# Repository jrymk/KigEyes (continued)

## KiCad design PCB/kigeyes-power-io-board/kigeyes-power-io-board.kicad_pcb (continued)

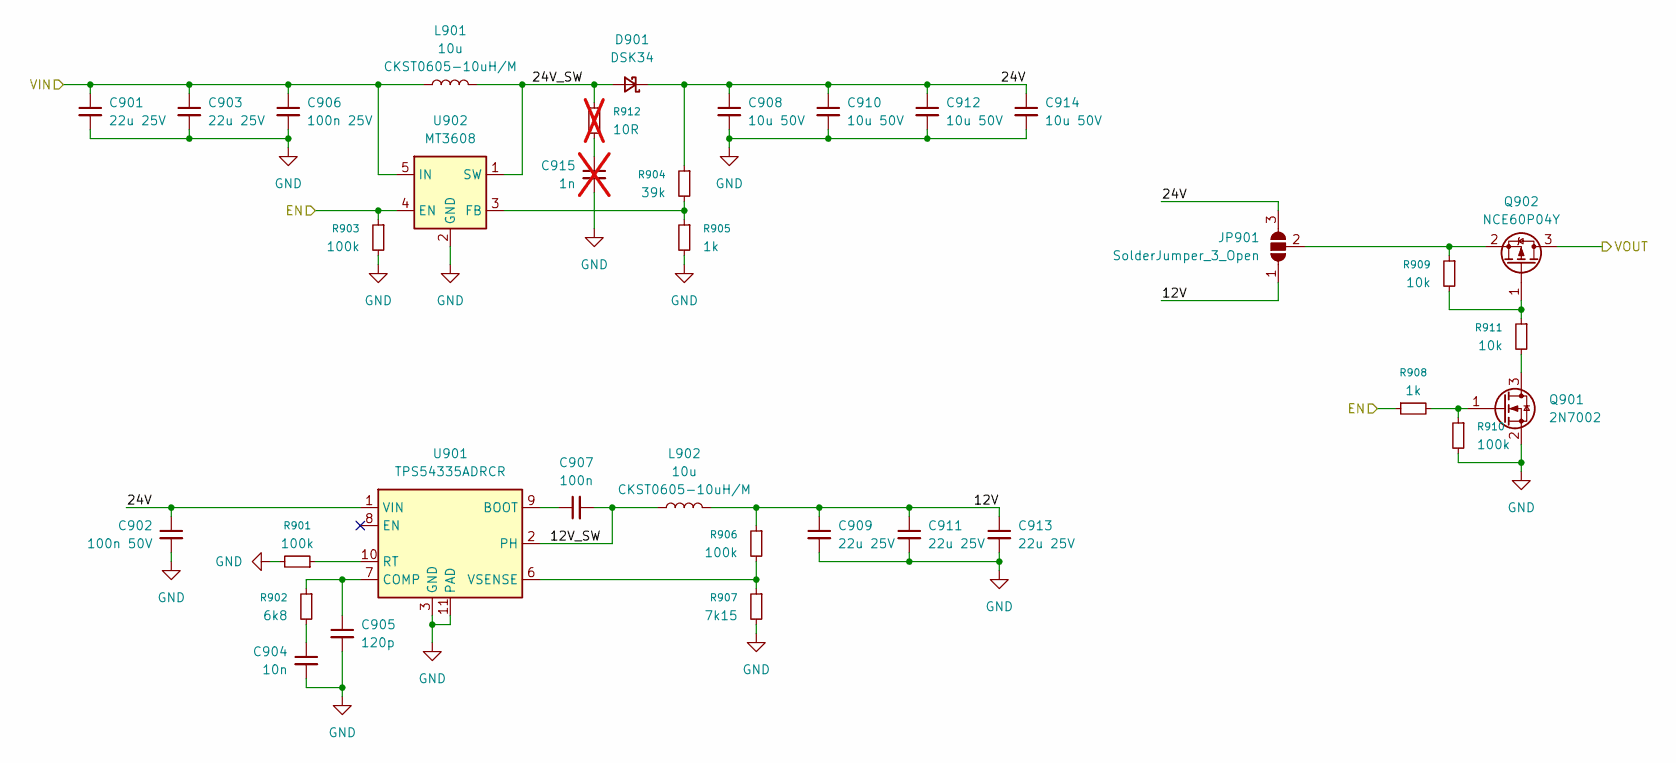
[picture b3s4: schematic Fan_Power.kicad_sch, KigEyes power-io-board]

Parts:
C901, C903, C909, C911, C913: 22u 25V; C_0805_2012Metric
C902: 100n 50V; C_0603_1608Metric
C904: 10n; C_0402_1005Metric
C905: 120p; C_0402_1005Metric
C906: 100n 25V; C_0603_1608Metric
C907: 100n; C_0402_1005Metric
C908, C910, C912, C914: 10u 50V; C_0805_2012Metric
C915: 1n; C_0402_1005Metric; not fitted
D901: DSK34; D_SOD-123FL
JP901: SolderJumper_3_Open; SolderJumper-3_P1.3mm_Open_RoundedPad1.0x1.5mm
L901, L902: 10u; L_CKST0605; Part No. CKST0605-10uH/M
Q901: 2N7002; SOT-23
Q902: NCE60P04Y; SOT-23
R901, R903, R906, R910: 100k; R_0402_1005Metric
R902: 6k8; R_0402_1005Metric
R904: 39k; R_0402_1005Metric
R905, R908: 1k; R_0402_1005Metric
R907: 7k15; R_0402_1005Metric
R909, R911: 10k; R_0402_1005Metric
R912: 10R; R_0402_1005Metric; not fitted
U901: TPS54335ADRCR; Texas_DRC0010J
U902: MT3608; SOT-23-6

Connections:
/AON_5V_OR_HV: C901.1, C903.1, C906.1, L901.1, U902.5 (IN); also elsewhere on the board
/FAN_EN: R903.1, R908.1, U902.4 (EN); also elsewhere on the board
/Fan Power/12V: C909.1, C911.1, C913.1, JP901.1 (A), L902.2, R906.1
/Fan Power/12V_SW: C907.2, L902.1, U901.2 (PH)
/Fan Power/24V: C902.1, C908.1, C910.1, C912.1, C914.1, D901.1 (K), JP901.3 (B), R904.1, U901.1 (VIN)
/Fan Power/24V_SW: D901.2 (A), L901.2, R912.1, U902.1 (SW)
/Fan Power/VOUT: Q902.3 (D); also elsewhere on the board
GND: C901.2, C902.2, C903.2, C904.2, C905.2, C906.2, C908.2, C909.2, C910.2, C911.2, C912.2, C913.2, C914.2, C915.2, Q901.2 (S), R901.2, R903.2, R905.2, R907.2, R910.2, U901.3 (GND), U901.4 (GND), U901.5 (GND), U901.11 (PAD), U902.2 (GND); also elsewhere on the board
unnamed: C904.1, R902.2
unnamed: C915.1, R912.2
unnamed: JP901.2 (C), Q902.2 (S), R909.1
unnamed: Q901.3 (D), R911.2
unnamed: Q901.1 (G), R908.2, R910.1
unnamed: Q902.1 (G), R909.2, R911.1
unnamed: C907.1, U901.9 (BOOT)
unnamed: C905.1, R902.1, U901.7 (COMP)
unnamed: R901.1, U901.10 (RT)
unnamed: R906.2, R907.1, U901.6 (VSENSE)
unnamed: R904.2, R905.1, U902.3 (FB)

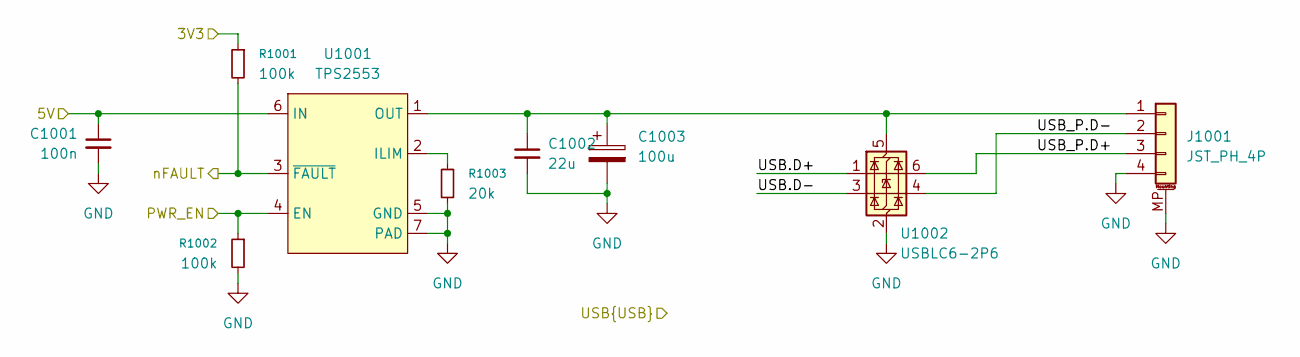
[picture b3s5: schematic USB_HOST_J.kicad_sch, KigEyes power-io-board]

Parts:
C1001: 100n; C_0402_1005Metric
C1002: 22u; C_0603_1608Metric
C1003: 100u; CP_Elec_6.3x5.8
J1001: JST_PH_4P; JST_PH_S4B-PH-SM4-TB_1x04-1MP_P2.00mm_Horizontal
R1001, R1002: 100k; R_0402_1005Metric
R1003: 20k; R_0402_1005Metric
U1001: TPS2553; WSON-6-1EP_2x2mm_P0.65mm_EP1x1.6mm
U1002: USBLC6-2P6; SOT-666

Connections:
+3V3: R1001.1; also elsewhere on the board
+5V: C1001.1, U1001.6 (IN); also elsewhere on the board
/PORT3_OCS: R1001.2, U1001.3 (~FAULT); also elsewhere on the board
/PORT3_PWR: R1002.1, U1001.4 (EN); also elsewhere on the board
/USB_HOST_J.D+: U1002.1 (I/O1); also elsewhere on the board
/USB_HOST_J.D-: U1002.3 (I/O2); also elsewhere on the board
/USB_HOST_J/USB_P.D+: J1001.3, U1002.6 (I/O1)
/USB_HOST_J/USB_P.D-: J1001.2, U1002.4 (I/O2)
GND: C1001.2, C1002.2, C1003.2, J1001.4, J1001.MP (MountPin), R1002.2, R1003.2, U1001.5 (GND), U1001.7 (PAD), U1002.2 (GND); also elsewhere on the board
unnamed: C1002.1, C1003.1, J1001.1, U1001.1 (OUT), U1002.5 (VBUS)
unnamed: R1003.1, U1001.2 (ILIM)

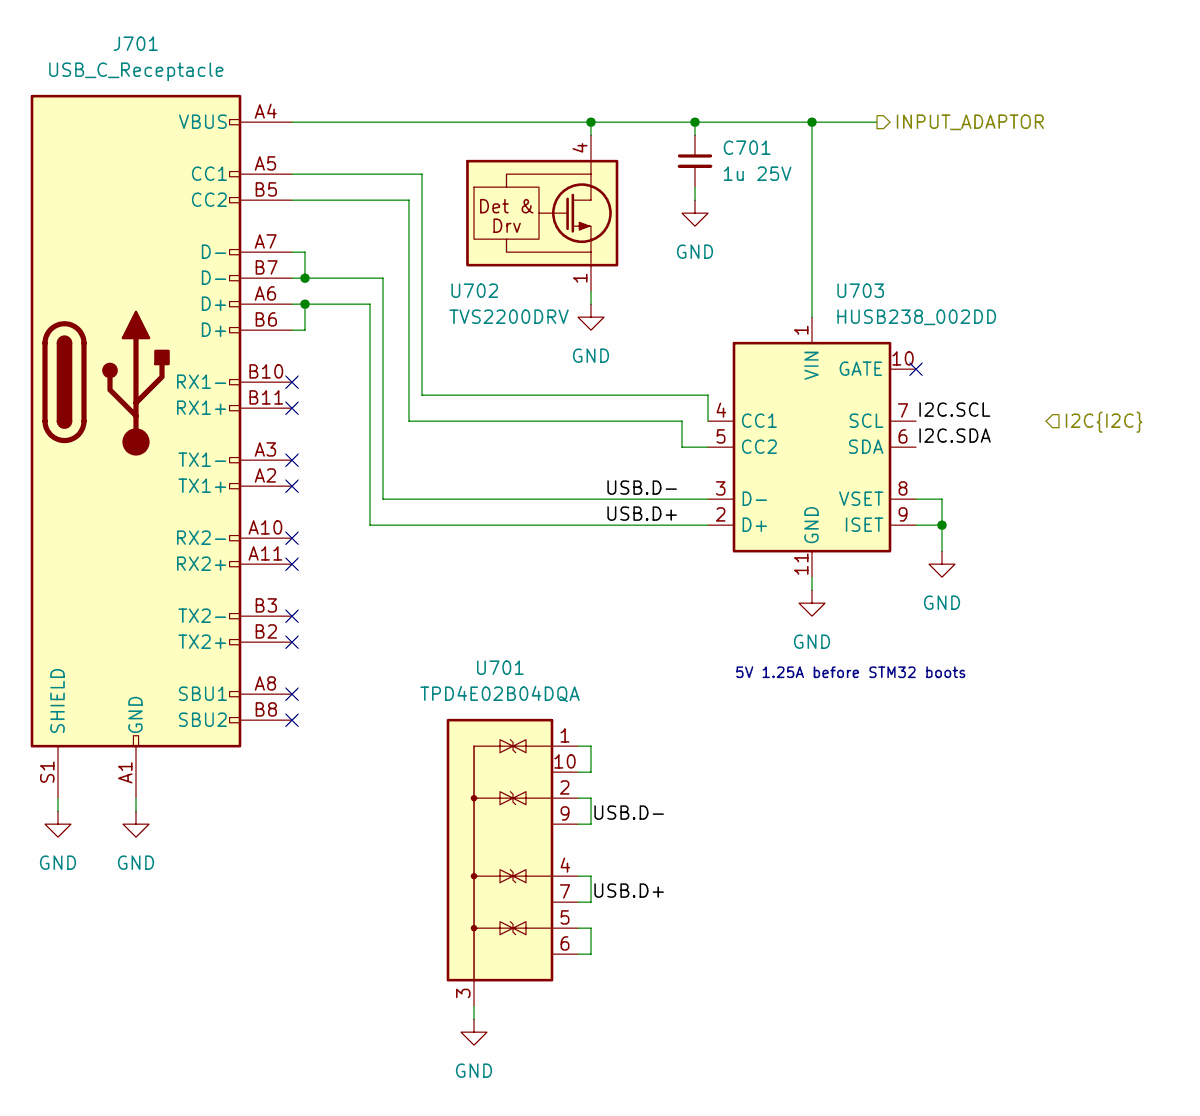
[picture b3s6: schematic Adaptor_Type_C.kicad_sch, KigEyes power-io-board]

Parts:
C701: 1u 25V; C_0603_1608Metric
J701: USB_C_Receptacle; USB_C_Receptacle_GCT_USB4080
U701: TPD4E02B04DQA; Texas USON-10_2.5x1.0mm_P0.5mm DQA0010A
U702: TVS2200DRV; WSON-6-1EP_2x2mm_P0.65mm_EP1x1.6mm
U703: HUSB238_002DD; WDFN-10-1EP_3x3mm_P0.5mm_EP1.8x2.5mm

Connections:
/Adaptor Type C/USB.D+: J701.A6 (D+), J701.B6 (D+), U701.4 (IO3), U701.7 (NC), U703.2 (D+)
/Adaptor Type C/USB.D-: J701.A7 (D-), J701.B7 (D-), U701.2 (IO2), U701.9 (NC), U703.3 (D-)
/I2C.SCL: U703.7 (SCL); also elsewhere on the board
/I2C.SDA: U703.6 (SDA); also elsewhere on the board
/INPUT_ADAPTOR: C701.1, J701.A4 (VBUS), J701.A9 (VBUS), J701.B4 (VBUS), J701.B9 (VBUS), U702.4 (IN), U702.5 (IN), U702.6 (IN), U703.1 (VIN); also elsewhere on the board
GND: C701.2, J701.A1 (GND), J701.A12 (GND), J701.B1 (GND), J701.B12 (GND), J701.S1 (SHIELD), U701.3 (G), U701.8 (G), U702.1 (GND), U702.2 (GND), U702.3 (GND), U702.7 (GND), U703.8 (VSET), U703.9 (ISET), U703.11 (GND); also elsewhere on the board
unnamed: J701.A5 (CC1), U703.4 (CC1)
unnamed: J701.B5 (CC2), U703.5 (CC2)
unnamed: U701.1 (IO1), U701.10 (NC)
unnamed: U701.5 (IO4), U701.6 (NC)

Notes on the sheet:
5V 1.25A before STM32 boots

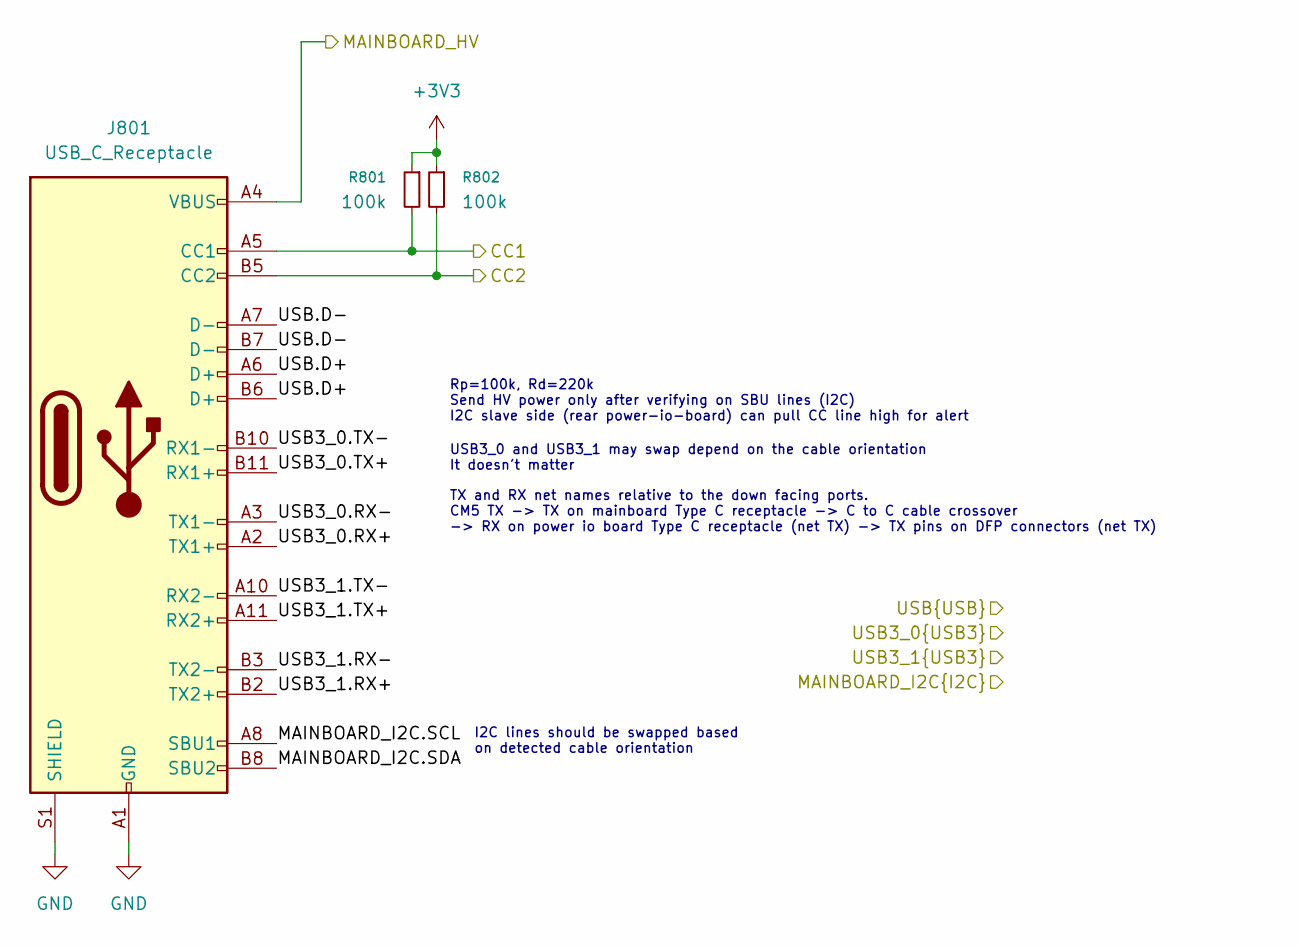
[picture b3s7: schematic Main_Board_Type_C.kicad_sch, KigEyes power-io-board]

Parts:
J801: USB_C_Receptacle; USB_C_Receptacle_GCT_USB4080
R801, R802: 100k; R_0402_1005Metric

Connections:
+3V3: R801.1, R802.1; also elsewhere on the board
/CC1: J801.A5 (CC1), R801.2; also elsewhere on the board
/CC2: J801.B5 (CC2), R802.2; also elsewhere on the board
/MAINBOARD_HV: J801.A4 (VBUS), J801.A9 (VBUS), J801.B4 (VBUS), J801.B9 (VBUS); also elsewhere on the board
/MAINBOARD_I2C.SCL: J801.A8 (SBU1); also elsewhere on the board
/MAINBOARD_I2C.SDA: J801.B8 (SBU2); also elsewhere on the board
/USB3_0.RX+: J801.A2 (TX1+); also elsewhere on the board
/USB3_0.RX-: J801.A3 (TX1-); also elsewhere on the board
/USB3_0.TX+: J801.B11 (RX1+); also elsewhere on the board
/USB3_0.TX-: J801.B10 (RX1-); also elsewhere on the board
/USB3_1.RX+: J801.B2 (TX2+); also elsewhere on the board
/USB3_1.RX-: J801.B3 (TX2-); also elsewhere on the board
/USB3_1.TX+: J801.A11 (RX2+); also elsewhere on the board
/USB3_1.TX-: J801.A10 (RX2-); also elsewhere on the board
/USB.D+: J801.A6 (D+), J801.B6 (D+); also elsewhere on the board
/USB.D-: J801.A7 (D-), J801.B7 (D-); also elsewhere on the board
GND: J801.A1 (GND), J801.A12 (GND), J801.B1 (GND), J801.B12 (GND), J801.S1 (SHIELD); also elsewhere on the board

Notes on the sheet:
TX and RX net names relative to the down facing ports. CM5 TX -> TX on mainboard Type C receptacle -> C to C cable crossover -> RX on power io board Type C receptacle (net TX) -> TX pins on DFP connectors (net TX)
I2C lines should be swapped based on detected cable orientation
Rp=100k, Rd=220k Send HV power only after verifying on SBU lines (I2C) I2C slave side (rear power-io-board) can pull CC line high for alert
USB3_0 and USB3_1 may swap depend on the cable orientation It doesn't matter

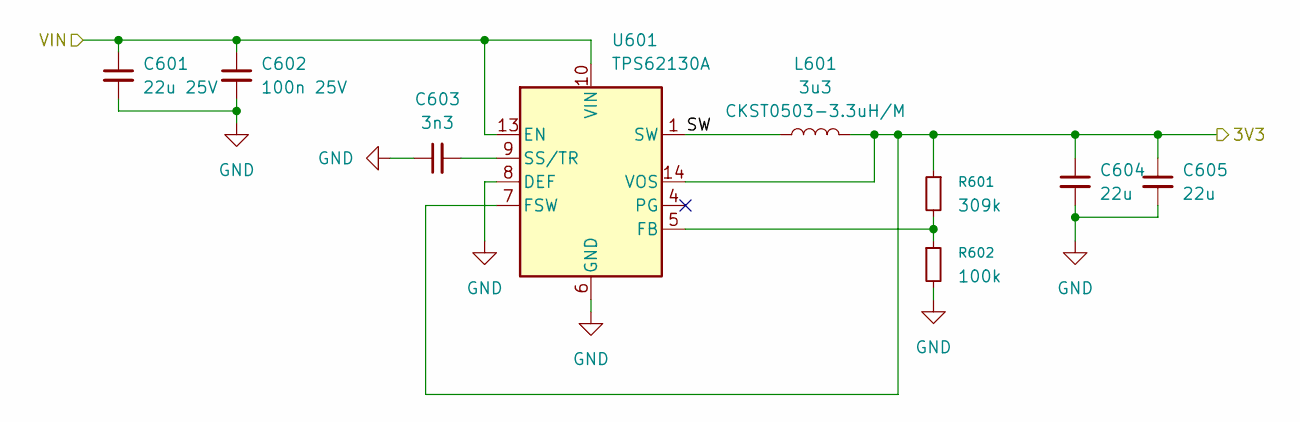
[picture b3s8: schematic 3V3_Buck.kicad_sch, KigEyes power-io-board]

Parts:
C601: 22u 25V; C_0805_2012Metric
C602: 100n 25V; C_0603_1608Metric
C603: 3n3; C_0402_1005Metric
C604, C605: 22u; C_0603_1608Metric
L601: 3u3; L_CKST0503; Part No. CKST0503-3.3uH/M
R601: 309k; R_0402_1005Metric
R602: 100k; R_0402_1005Metric
U601: TPS62130A; VQFN-16-1EP_3x3mm_P0.5mm_EP1.68x1.68mm

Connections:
+3V3: C604.1, C605.1, L601.2, R601.1, U601.7 (FSW), U601.14 (VOS); also elsewhere on the board
/3V3 Buck/SW: L601.1, U601.1 (SW), U601.2 (SW), U601.3 (SW)
/AON_5V_OR_HV: C601.1, C602.1, U601.10 (VIN), U601.11 (VIN), U601.12 (VIN), U601.13 (EN); also elsewhere on the board
GND: C601.2, C602.2, C603.1, C604.2, C605.2, R602.2, U601.6 (GND), U601.8 (DEF), U601.15 (GND), U601.16 (GND), U601.17 (GND); also elsewhere on the board
unnamed: R601.2, R602.1, U601.5 (FB)
unnamed: C603.2, U601.9 (SS/TR)

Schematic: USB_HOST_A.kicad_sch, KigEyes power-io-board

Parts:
C301: 100n; C_0402_1005Metric
C302: 22u; C_0603_1608Metric
C303: 100u; CP_Elec_6.3x5.8
J301: USB3_A; USB3_A_GCT-USB1135
R301, R302: 100k; R_0402_1005Metric
R303: 20k; R_0402_1005Metric
U301: TPS2553; WSON-6-1EP_2x2mm_P0.65mm_EP1x1.6mm
U302: USBLC6-2P6; SOT-666
U303: TPD4E02B04DQA; Texas USON-10_2.5x1.0mm_P0.5mm DQA0010A

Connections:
+3V3: R301.1; also elsewhere on the board
+5V: C301.1, U301.6 (IN); also elsewhere on the board
/PORT2_OCS: R301.2, U301.3 (~FAULT); also elsewhere on the board
/PORT2_PWR: R302.1, U301.4 (EN); also elsewhere on the board
/USB3_1.RX+: J301.6 (SSRX+), U303.2 (IO2), U303.9 (NC); also elsewhere on the board
/USB3_1.RX-: J301.5 (SSRX-), U303.1 (IO1), U303.10 (NC); also elsewhere on the board
/USB3_1.TX+: J301.9 (SSTX+), U303.5 (IO4), U303.6 (NC); also elsewhere on the board
/USB3_1.TX-: J301.8 (SSTX-), U303.4 (IO3), U303.7 (NC); also elsewhere on the board
/USB_HOST_A.D+: U302.6 (I/O1); also elsewhere on the board
/USB_HOST_A.D-: U302.4 (I/O2); also elsewhere on the board
/USB_HOST_A/USB_P.D+: J301.3 (D+), U302.1 (I/O1)
/USB_HOST_A/USB_P.D-: J301.2 (D-), U302.3 (I/O2)
GND: C301.2, C302.2, C303.2, J301.4 (GND), J301.7 (DRAIN), J301.SH (SHIELD), R302.2, R303.2, U301.5 (GND), U301.7 (PAD), U302.2 (GND), U303.3 (G), U303.8 (G); also elsewhere on the board
unnamed: C302.1, C303.1, J301.1 (VBUS), U301.1 (OUT), U302.5 (VBUS)
unnamed: R303.1, U301.2 (ILIM)

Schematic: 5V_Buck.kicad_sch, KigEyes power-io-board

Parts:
C501, C502, C503: 22u 25V; C_0805_2012Metric
C504: 100n 25V; C_0603_1608Metric
C505: 47n; C_0402_1005Metric
C506: 1u; C_0402_1005Metric
C507: 100n; C_0402_1005Metric
C508: 47p; C_0402_1005Metric
C509, C510: 100u; C_1210_3225Metric
L501: 2u2; L_CKST1004; Part No. CKST1004-2.2uH/M
R501: 330k; R_0402_1005Metric
R502, R505: 15k; R_0402_1005Metric
R503: 100k; R_0402_1005Metric
R504: 110k; R_0402_1005Metric
U501: TPS56C230; VQFN-20_EP_3x3_Pitch0.45mm_RJE0020B

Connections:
+5V: C508.1, C509.1, C510.1, L501.2, R504.1; also elsewhere on the board
/5V Buck/PGOOD: U501.9 (PGOOD)
/5V Buck/SW: C507.2, L501.1, U501.6 (SW), U501.19 (SW), U501.20 (SW)
/5V Buck/VCC: C506.2, R501.1, U501.17 (VCC)
/5V_EN: R503.1, U501.12 (EN); also elsewhere on the board
/AON_5V_OR_HV: C501.1, C502.1, C503.1, C504.1, U501.2 (VIN), U501.3 (VIN), U501.4 (VIN), U501.5 (VIN); also elsewhere on the board
GND: C501.2, C502.2, C503.2, C504.2, C505.2, C506.1, C509.2, C510.2, R502.2, R503.2, R505.2, U501.7 (PGND), U501.8 (PGND), U501.10 (NC), U501.13 (AGND), U501.16 (NC), U501.18 (PGND), U501.21 (PGND); also elsewhere on the board
unnamed: C507.1, U501.1 (BST)
unnamed: C508.2, R504.2, R505.1, U501.14 (FB)
unnamed: R501.2, R502.1, U501.15 (MODE)
unnamed: C505.1, U501.11 (SS)

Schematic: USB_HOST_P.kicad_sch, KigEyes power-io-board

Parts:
C1102: 22u; C_0603_1608Metric
J1101: Conn_01x04_MountingPin; JST_PH_B4B-PH-K_1x04_P2.00mm_Vertical
U1102: USBLC6-2P6; SOT-666

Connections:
+5V: C1102.1, J1101.1, U1102.5 (VBUS); also elsewhere on the board
/USB_HOST_P.D+: U1102.1 (I/O1); also elsewhere on the board
/USB_HOST_P.D-: U1102.3 (I/O2); also elsewhere on the board
/USB_HOST_P/USB_P.D+: J1101.3, U1102.6 (I/O1)
/USB_HOST_P/USB_P.D-: J1101.2, U1102.4 (I/O2)
GND: C1102.2, J1101.4, U1102.2 (GND); also elsewhere on the board

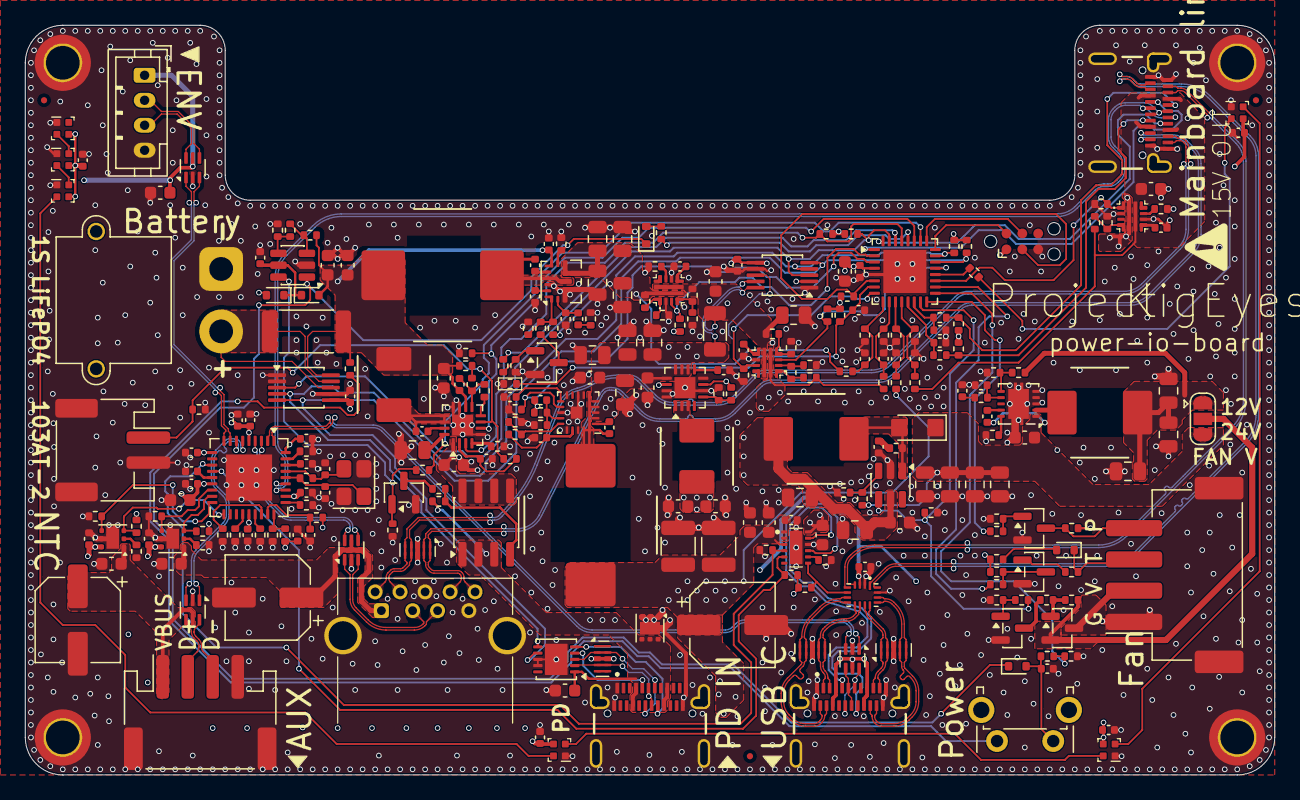
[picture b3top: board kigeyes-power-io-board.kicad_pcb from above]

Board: 4 copper layers, 100.0 x 60.0 mm, 280 parts (0 on the bottom side), 184 nets.

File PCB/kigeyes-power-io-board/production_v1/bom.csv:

Designator,Footprint,Quantity,Value,LCSC Part #
"C1001, C103, C105, C122, C128, C129, C132, C204, C205, C301, C403, C404, C408, C409, C410, C411, C412, C413, C507, C907",0402,20,100n,
"C1002, C101, C102, C1102, C202, C203, C302, C604, C605",0603,9,22u,
"C1003, C201, C303",CP_Elec_6.3x5.8,3,100u,
"C104, C107",0402,2,2u2,
"C106, C126, C133",0603,3,2u2 25V,
C108,0402,1,1n,
"C109, C110, C114, C120, C123, C131, C139",0402,7,10n,
C111,0805,1,10u 25V,
C112,0402,1,30p,
"C113, C116, C119, C121, C501, C502, C503, C601, C901, C903, C909, C911, C913",0805,13,22u 25V,
"C115, C505",0402,2,47n,
C117,0402,1,470p,
C118,0603,1,10u,
"C124, C125, C130, C603",0402,4,3n3,
"C127, C206, C414",0603,3,4u7,
"C134, C135, C136, C137, C138, C406, C407, C506",0402,8,1u,
"C401, C402",0402,2,15p,
C405,0402,1,220n,
"C504, C602, C906",0603,3,100n 25V,
C508,0402,1,47p,
"C509, C510",1210,2,100u,
C701,0603,1,1u 25V,
C902,0603,1,100n 50V,
C904,0402,1,12n,
C905,0402,1,120p,
"C908, C910, C912, C914",0805,4,10u 50V,
"D101, D102, D103, D104, D105",D_SOD-523,5,SD103AWT,
"D106, D107, D108, D109, D110, D111",WS2812B-1515,6,WS2812B,
D901,D_SOD-123FL,1,DSK34,
J1001,JST_PH_S4B-PH-SM4-TB_1x04-1MP_P2.00mm_Horizontal,1,Conn_01x04_MountingPin,
J101,JST_PH_S2B-PH-SM4-TB_1x02-1MP_P2.00mm_Horizontal,1,Conn_01x02_MountingPin,
J102,AMASS_XT30PW-M_1x02_P2.50mm_Horizontal,1,XT30,
J104,JST_XH_S4B-XH-SM4-TB_1x04-1MP_P2.50mm_Horizontal,1,JST_PH_4P,
J1101,JST_PH_B4B-PH-K_1x04_P2.00mm_Vertical,1,Conn_01x04_MountingPin,
"J201, J701, J801",USB_C_Receptacle_GCT_USB4080,3,USB_C_Receptacle,
J301,USB3_A_GCT-USB1135,1,USB3_A,
"L101, L501",L_CKST1004,2,2u2,
L102,L_CKST0503,1,2u2,
L601,L_CKST0503,1,3u3,
"L901, L902",L_CKST0605,2,10u,
"Q101, Q104, Q901",SOT-23,3,2N7002,
Q102,SOP-8_3.76x4.96mm_P1.27mm_NCE40P13S,1,NCE40P13S,
Q103,SOT-23,1,AO3400A,
Q105,SOT-23,1,MMBT3904,
Q902,SOT-23,1,NCE60P04Y,
"R1001, R1002, R104, R106, R113, R118, R131, R135, R140, R150, R161, R162, R163, R165, R168, R169, R201, R202, R203, R204, R301, R302, R402, R403, R404, R405, R406, R407, R409, R503, R602, R801, R802, R901, R903, R906, R910",0402,37,100k,
"R1003, R303",0402,2,20k,
"R101, R119, R130, R147, R905, R908",0402,6,1k,
"R102, R103, R105, R146, R155, R909, R911",0402,7,10k,
R107,0402,1,2k2,
"R108, R109, R139, R152, R153",0402,5,4k7,
R110,0402,1,140k,
R111,0402,1,19k1,
R112,0402,1,36k5,
R114,0402,1,13k3,
R115,0402,1,14k,
"R116, R122, R125, R128, R142, R144, R156, R501",0402,8,330k,
"R117, R126, R129, R904",0402,4,39k,
R120,0402,1,4k53,
R121,0402,1,23k2,
R123,0402,1,75k,
R124,0402,1,180k,
R127,2512,1,2m,
"R132, R401",0402,2,1M,
R133,0402,1,280k,
R134,0402,1,249k,
"R137, R138, R154",0402,3,560R,
"R141, R151, R166",0402,3,33k,
"R143, R145, R157",0402,3,68k,
R148,0805,1,10k,
R149,1206,1,3m,
R158,0402,1,820k,
R159,0402,1,51k,
R160,0402,1,105k,
R164,0402,1,220R,
R167,0402,1,200k,
R408,0402,1,12k,
"R502, R505",0402,2,15k,
R504,0402,1,110k,
R601,0402,1,312k,
R902,0402,1,6k8,
R907,0402,1,7k15,
SW101,SW_Tactile_SPST_Angled_PTS645Vx58-2LFS,1,SW_Push,
TH101,0402,1,Thermistor_NTC,
"U1001, U301",WSON-6-1EP_2x2mm_P0.65mm_EP1x1.6mm,2,TPS2553,
"U1002, U1102, U204, U302",SOT-666,4,USBLC6-2P6,
U101,Texas_VQFN-HR-20_3x2.5mm_P0.5mm_RQQ0011A,1,TPS61288,
U102,WQFN-16-1EP_3x3mm_P0.5mm_EP1.68x1.68mm,1,BQ25306,
"U103, U107",TSSOP-10_3x3mm_P0.5mm,2,INA226,
"U104, U105, U108",Texas VQFN-HR 2x2mm RPW0010A,3,LM73100,
U106,QFN-32-1EP_5x5mm_P0.5mm_EP3.45x3.45mm,1,STM32G071KBUx,
U109,SOT-23-6,1,TPS3700,
U201,Texas WSON-12 P0.5mm 3x2mm EP2.65x1mm DSS0012B,1,TPS25820,
U202,Texas UQFN-16_1.8x2.6mm_P0.4mm RSV0016A,1,HD3SS3202,
"U203, U205, U303, U701",Texas USON-10_2.5x1.0mm_P0.5mm DQA0010A,4,TPD4E02B04DQA,
U401,QFN-36-1EP_6x6mm_P0.5mm_EP3.7x3.7mm,1,USB2514B_Bi,
U501,VQFN-20_EP_3x3_Pitch0.45mm_RJE0020B,1,TPS56C230,
U601,VQFN-16-1EP_3x3mm_P0.5mm_EP1.68x1.68mm,1,TPS62130A,
U702,WSON-6-1EP_2x2mm_P0.65mm_EP1x1.6mm,1,TVS2200DRV,
U703,WDFN-10-1EP_3x3mm_P0.5mm_EP1.8x2.5mm,1,HUSB238_002DD,
U901,Texas_DRC0010J,1,TPS54335ADRCR,
U902,SOT-23-6,1,MT3608,
Y401,Crystal_SMD_SeikoEpson_FA238-4Pin_3.2x2.5mm,1,24MHz 10pF,
